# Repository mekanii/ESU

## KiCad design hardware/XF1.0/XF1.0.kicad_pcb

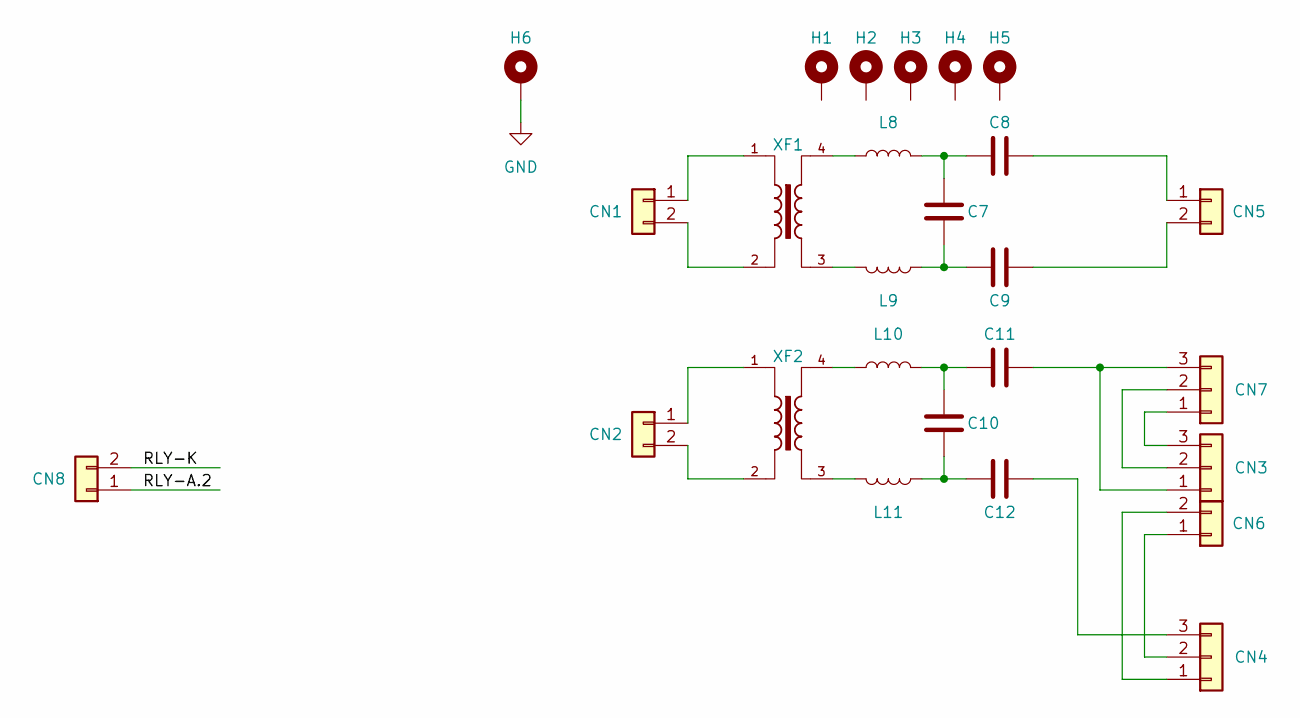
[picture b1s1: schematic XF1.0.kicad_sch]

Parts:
C7, C10: 2.7nF; C_Rect_L18.0mm_W7.0mm_P15.00mm_FKS3_FKP3
C8, C9, C11, C12: 4.7nF; C_Rect_L18.0mm_W7.0mm_P15.00mm_FKS3_FKP3
CN1, CN2, CN5, CN6: Conn_01x02; Molex_KK-396_5273-03A_1x03_P3.96mm_Vertical_2
CN3, CN4, CN7: Conn_01x03; Molex_KK-396_5273-05A_1x05_P3.96mm_Vertical_2
CN8: Conn_01x02; Molex_KK-396_5273-02A_1x02_P3.96mm_Vertical
H1, H2, H3, H4, H5, H6: MountingHole_3mm_Pad
L8, L9, L10, L11: 29µH; L_Radial_Multilayer_D8.0mm_P12.70mm
XF1, XF2: Transformer_Toroid_Horizontal_OD40_ID23_H15

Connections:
/RLY-A.2: CN8.1
/RLY-K: CN8.2
GND: H6.1
unnamed: C7.1, C8.1, L8.2
unnamed: C7.2, C9.1, L9.2
unnamed: C10.1, C11.1, L10.2
unnamed: C10.2, C12.1, L11.2
unnamed: CN1.1, XF1.1
unnamed: CN1.2, XF1.2
unnamed: CN2.1, XF2.1
unnamed: CN2.2, XF2.2
unnamed: C11.2, CN3.1, CN7.3
unnamed: CN3.2, CN7.2
unnamed: CN3.3, CN7.1
unnamed: CN4.1, CN6.2
unnamed: CN4.2, CN6.1
unnamed: C12.2, CN4.3
unnamed: C8.2, CN5.1
unnamed: C9.2, CN5.2
unnamed: L8.1, XF1.4
unnamed: L9.1, XF1.3
unnamed: L10.1, XF2.4
unnamed: L11.1, XF2.3

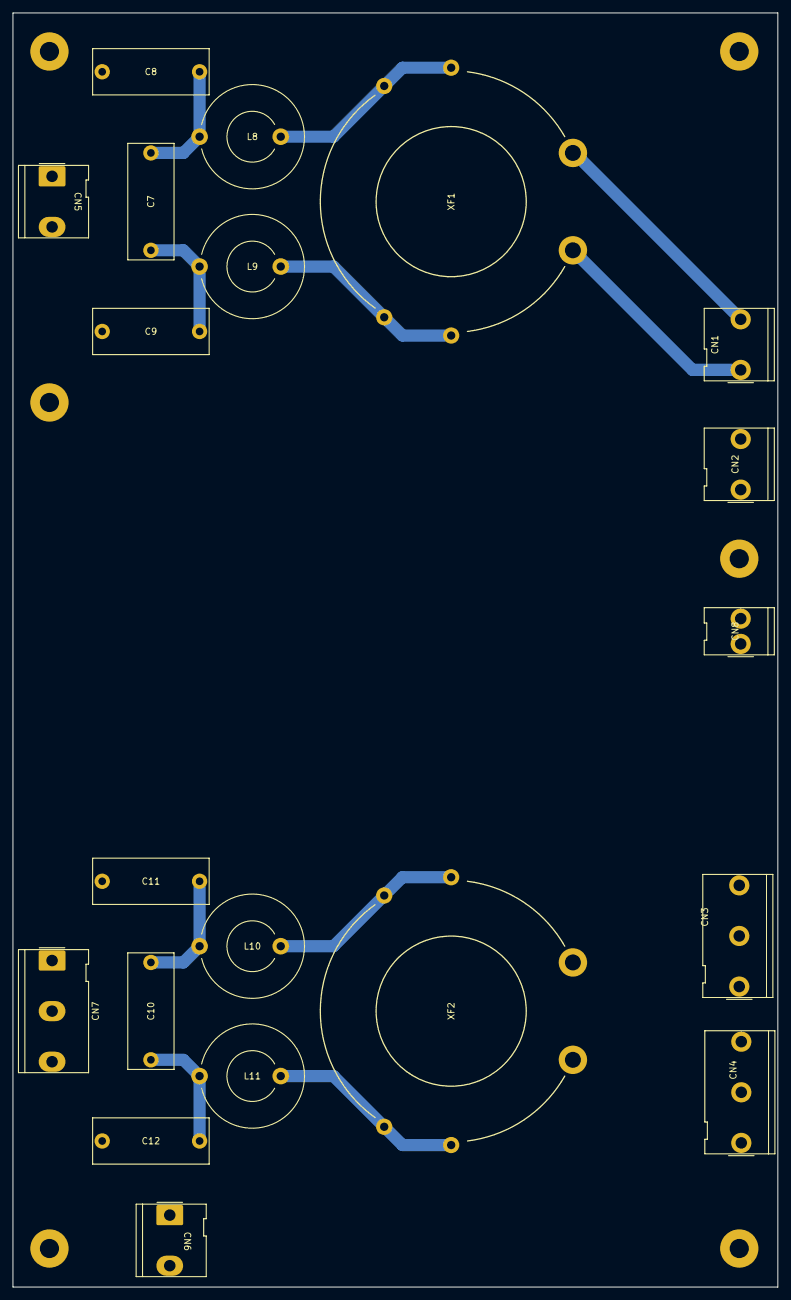
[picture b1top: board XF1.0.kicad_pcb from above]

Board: 2 copper layers, 119.7 x 199.4 mm, 26 parts (0 on the bottom side), 20 nets.
